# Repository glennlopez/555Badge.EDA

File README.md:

# 555Badge.EDA

<!-- Tutorial Links:
    - https://www.youtube.com/watch?v=c2niS9ZRBHo&list=PL3bNyZYHcRSUhUXUt51W6nKvxx2ORvUQB&index=2
>

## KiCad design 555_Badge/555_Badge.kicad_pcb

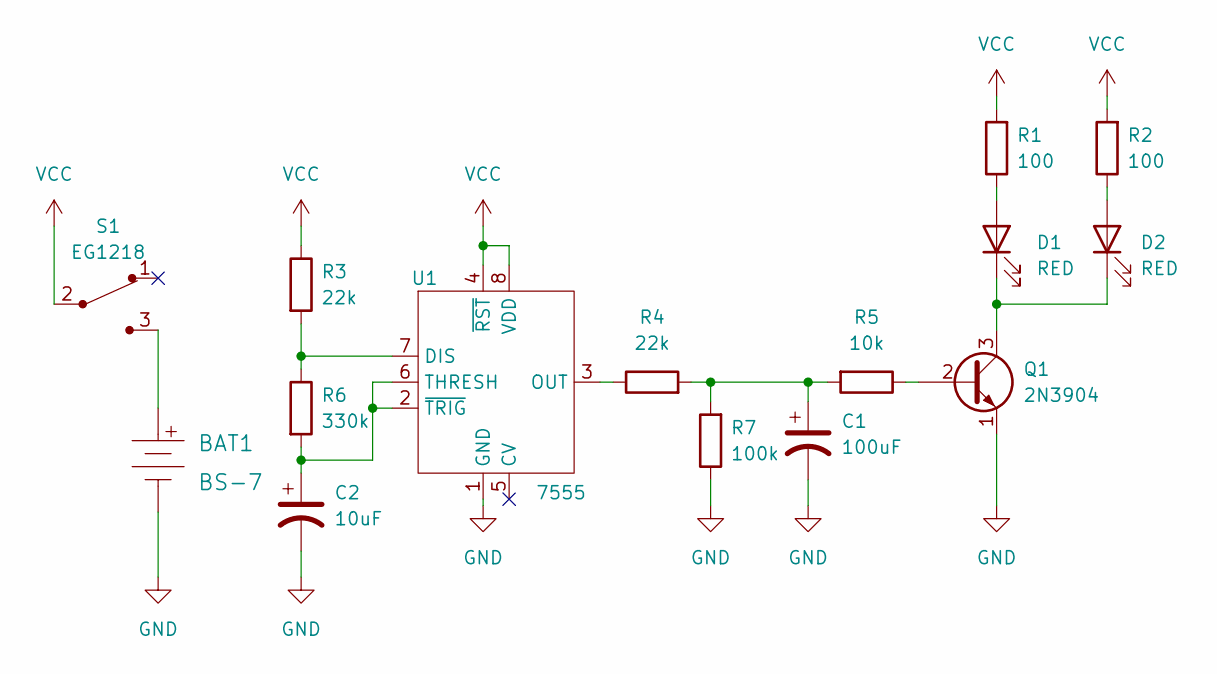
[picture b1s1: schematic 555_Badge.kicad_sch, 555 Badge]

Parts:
BAT1: BS-7; Battery_Holder_Coin_2032_BS-7; MPN BS-7; Digi-Key_PN BS-7-ND
C1: 100uF; CP_Radial_D6.3mm_P2.50mm
C2: 10uF; CP_Radial_D5.0mm_P2.00mm
D1, D2: RED; LED_D3.0mm
Q1: 2N3904; TO-92-3
R1, R2: 100; R_Axial_DIN0207_L6.3mm_D2.5mm_P7.62mm_Horizontal
R3, R4: 22k; R_Axial_DIN0207_L6.3mm_D2.5mm_P7.62mm_Horizontal
R5: 10k; R_Axial_DIN0207_L6.3mm_D2.5mm_P7.62mm_Horizontal
R6: 330k; R_Axial_DIN0207_L6.3mm_D2.5mm_P7.62mm_Horizontal
R7: 100k; R_Axial_DIN0207_L6.3mm_D2.5mm_P7.62mm_Horizontal
S1: EG1218; Switch_Slide_11.6x4mm_EG1218; MPN EG1218; Digi-Key_PN EG1903-ND
U1: 7555; ICM7555-PDIP

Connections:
GND: BAT1.Neg, C1.2, C2.2, Q1.1 (E), R7.1, U1.1 (GND)
unnamed: BAT1.Pos, S1.3
unnamed: C1.1, R4.2, R5.2, R7.2
unnamed: D1.1 (K), D2.1 (K), Q1.3 (C)
unnamed: D1.2 (A), R1.1
unnamed: D2.2 (A), R2.1
unnamed: Q1.2 (B), R5.1
unnamed: R3.2, R6.1, U1.7 (DIS)
unnamed: R4.1, U1.3 (OUT)
unnamed: C2.1, R6.2, U1.2 (~TRIG), U1.6 (THRESH)
VCC: R1.2, R2.2, R3.1, S1.2, U1.4 (~RST), U1.8 (VDD)

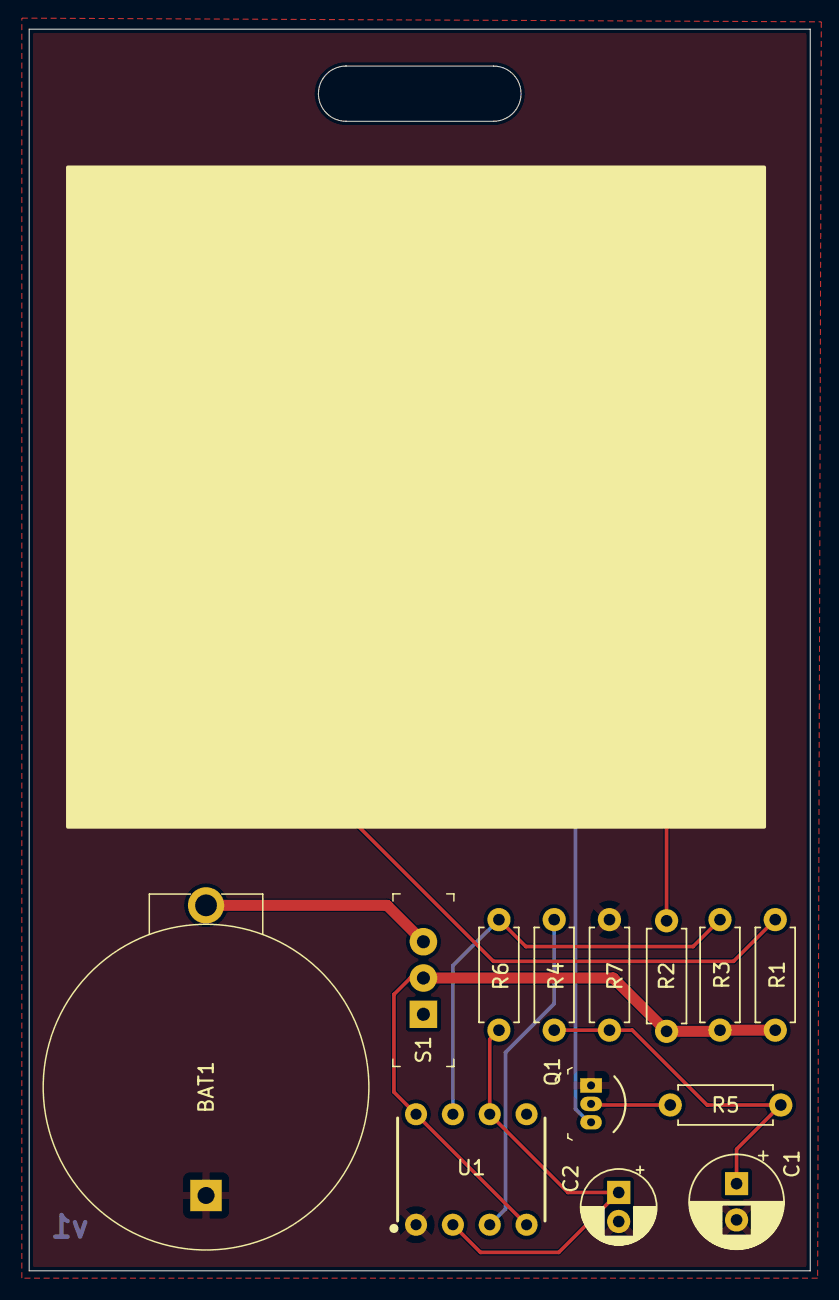
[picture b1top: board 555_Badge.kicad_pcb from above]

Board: 2 copper layers, 53.8 x 85.6 mm, 15 parts (0 on the bottom side), 11 nets.

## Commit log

2022-12-18 init commit
    initial commit for 555 badge
2022-12-19 finished 555 symbol
2022-12-20 finished schematic capture
2022-12-21 finished creating footprint for 7555 PDIP
2022-12-22 associated footprints and updated pcb from schematic
    in kicad 6 you no longer need to generate netlist to use for pcb
2022-12-23 setup pcb layout
    added jclpcb drc design rule
2022-12-29 pcb parts placement and board outline definition
2023-01-01 boardlayout complete

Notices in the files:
555_Badge/555_Badge.kicad_pcb:
License: CC by 4.0
